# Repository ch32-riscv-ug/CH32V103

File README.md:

# CH32V103

<!-- This file is generated from ch32-riscv-ug/ch32-device-data (index/ + evidence/ + tools/build_readme.py). Edit there, not here. -->

[Choose a part](#product-comparison) &middot; [Pin viewer](https://ch32-riscv-ug.github.io/ch32-device-data/pins.html?chip=CH32V103) &middot; [Pin maps](#pin-maps--alternate-functions) &middot; [Examples](#evt-examples) &middot; [Documents](#documents) &middot; [Address map](#address-map)

## Quick start

Programming and debug: **2-wire SDI** (WCH-Link, `Serial Debug Interface`).

### Debug / serial defaults

Where these land **without writing a remap register**. SWD is live at reset; the UART pads are not -- the pin must still be put into alternate-function mode. See `route` in evidence/README.ja.md.

| Series | SWDIO | SWCLK | UART TX | UART RX |
|---|---|---|---|---|
| CH32V103 | PA13 | PA14 | PA9 (USART1); PA2 (USART2) | PA10 (USART1); PA3 (USART2) |

## Series

Flash and SRAM list every value the series has; more than one means it varies by part number, and the per-part values are in the comparison table below.

| Series | Core | ISA | Flash | SRAM | Main clock | VDD | Packages | Products | Official |
|---|---|---|---|---|---|---|---|---|---|
| **CH32V103** | QingKe V3A | RV32IMAC | 32K/64K | 10K/20K | 80 MHz | 2.7-5.5V | LQFP48,LQFP64M,QFN48X7 | 4 | [en](https://www.wch-ic.com/products/CH32V103.html) / [zh](https://www.wch.cn/products/CH32V103.html) |

## Product comparison

### CH32V103 product comparison

Only the 8 rows that differ between these 4 products; the other 7 are the same for all of them.

| | [CH32V103&#8203;C6T6](https://ch32-riscv-ug.github.io/ch32-device-data/pins.html?chip=CH32V103C6T6)&#8203;(LQFP48) | [CH32V103&#8203;C8T6](https://ch32-riscv-ug.github.io/ch32-device-data/pins.html?chip=CH32V103C8T6)&#8203;(LQFP48) | [CH32V103&#8203;C8U6](https://ch32-riscv-ug.github.io/ch32-device-data/pins.html?chip=CH32V103C8U6)&#8203;(QFN48X7) | [CH32V103&#8203;R8T6](https://ch32-riscv-ug.github.io/ch32-device-data/pins.html?chip=CH32V103R8T6)&#8203;(LQFP64M) |
|---|---|---|---|---|
| **Flash** | 32K | 64K | 64K | 64K |
| **SRAM** | 10K | 20K | 20K | 20K |
| **GPIO** | 37 | 37 | 37 | 51 |
| Timer General-purpose | 2 | 3 | 3 | 3 |
| ADC/TKey (Number of channels) | 10 | 10 | 10 | 16 |
| SPI | 1 | 2 | 2 | 2 |
| I2C | 1 | 2 | 2 | 2 |
| USART | 2 | 3 | 3 | 3 |

<details><summary>All 15 rows</summary>

| | [CH32V103&#8203;C6T6](https://ch32-riscv-ug.github.io/ch32-device-data/pins.html?chip=CH32V103C6T6)&#8203;(LQFP48) | [CH32V103&#8203;C8T6](https://ch32-riscv-ug.github.io/ch32-device-data/pins.html?chip=CH32V103C8T6)&#8203;(LQFP48) | [CH32V103&#8203;C8U6](https://ch32-riscv-ug.github.io/ch32-device-data/pins.html?chip=CH32V103C8U6)&#8203;(QFN48X7) | [CH32V103&#8203;R8T6](https://ch32-riscv-ug.github.io/ch32-device-data/pins.html?chip=CH32V103R8T6)&#8203;(LQFP64M) |
|---|---|---|---|---|
| **Flash** | 32K | 64K | 64K | 64K |
| **SRAM** | 10K | 20K | 20K | 20K |
| **GPIO** | 37 | 37 | 37 | 51 |
| **Temperature** | -40..85C | -40..85C | -40..85C | -40..85C |
| Timer General-purpose | 2 | 3 | 3 | 3 |
| Timer Advanced | 1 | 1 | 1 | 1 |
| Watchdog (WDT) | 2 | 2 | 2 | 2 |
| Timer SysTick | 1 | 1 | 1 | 1 |
| ADC/TKey (Number of channels) | 10 | 10 | 10 | 16 |
| SPI | 1 | 2 | 2 | 2 |
| I2C | 1 | 2 | 2 | 2 |
| USART | 2 | 3 | 3 | 3 |
| USBHD 2.0FS | 1 | 1 | 1 | 1 |
| CPU clock frequency | Typical: 72MHz | Typical: 72MHz | Typical: 72MHz | Typical: 72MHz |
| Operating voltage | 2.7V~5.5V | 2.7V~5.5V | 2.7V~5.5V | 2.7V~5.5V |

</details>

## Packages & pinout drawings

Pinout drawings are in the datasheet (chapter *Pinouts*); each link opens at the page that carries the drawing:

| Package | Products | Datasheet | Outline |
|---|---|---|---|
| LQFP48 | CH32V103C6T6 | [en](https://ch32-riscv-ug.github.io/CH32V103/datasheet_en/CH32V103DS0.PDF#page=13) / [zh](https://ch32-riscv-ug.github.io/CH32V103/datasheet_zh/CH32V103DS0.PDF#page=11) | [drawing](https://raw.githubusercontent.com/ch32-riscv-ug/WCH-common/main/image/package_LQFP48.png) |
| LQFP48 | CH32V103C8T6 | [en](https://ch32-riscv-ug.github.io/CH32V103/datasheet_en/CH32V103DS0.PDF#page=13) / [zh](https://ch32-riscv-ug.github.io/CH32V103/datasheet_zh/CH32V103DS0.PDF#page=11) | [drawing](https://raw.githubusercontent.com/ch32-riscv-ug/WCH-common/main/image/package_LQFP48.png) |
| QFN48X7 | CH32V103C8U6 | [en](https://ch32-riscv-ug.github.io/CH32V103/datasheet_en/CH32V103DS0.PDF#page=13) / [zh](https://ch32-riscv-ug.github.io/CH32V103/datasheet_zh/CH32V103DS0.PDF#page=11) | [drawing](https://raw.githubusercontent.com/ch32-riscv-ug/WCH-common/main/image/package_QFN48X7.png) |
| LQFP64M | CH32V103R8T6 | [en](https://ch32-riscv-ug.github.io/CH32V103/datasheet_en/CH32V103DS0.PDF#page=13) / [zh](https://ch32-riscv-ug.github.io/CH32V103/datasheet_zh/CH32V103DS0.PDF#page=11) | [drawing](https://raw.githubusercontent.com/ch32-riscv-ug/WCH-common/main/image/package_LQFP64M.png) |

## Pin maps & alternate functions

> [!NOTE]
> These are the **pin-table superset**: the datasheet prints one pad table for every product that shares a pinout, so a pad row does not mean this part has the peripheral. Use the product comparison table above for what a given part number contains.

### CH32V103 pin map

Pin functions (filterable): [ALL](https://ch32-riscv-ug.github.io/ch32-device-data/pins.html?chip=CH32V103) [ADC](https://ch32-riscv-ug.github.io/ch32-device-data/pins.html?chip=CH32V103&features=ADC) [I2C](https://ch32-riscv-ug.github.io/ch32-device-data/pins.html?chip=CH32V103&features=I2C) [SPI](https://ch32-riscv-ug.github.io/ch32-device-data/pins.html?chip=CH32V103&features=SPI) [SYS](https://ch32-riscv-ug.github.io/ch32-device-data/pins.html?chip=CH32V103&features=SYS) [TIM](https://ch32-riscv-ug.github.io/ch32-device-data/pins.html?chip=CH32V103&features=TIM) [UART](https://ch32-riscv-ug.github.io/ch32-device-data/pins.html?chip=CH32V103&features=UART) [USB](https://ch32-riscv-ug.github.io/ch32-device-data/pins.html?chip=CH32V103&features=USB)

| Pin name | Type | [CH32V103&#8203;C6T6](https://ch32-riscv-ug.github.io/ch32-device-data/pins.html?chip=CH32V103C6T6)&#8203;(LQFP48) | [CH32V103&#8203;C8T6](https://ch32-riscv-ug.github.io/ch32-device-data/pins.html?chip=CH32V103C8T6)&#8203;(LQFP48) | [CH32V103&#8203;C8U6](https://ch32-riscv-ug.github.io/ch32-device-data/pins.html?chip=CH32V103C8U6)&#8203;(QFN48X7) | [CH32V103&#8203;R8T6](https://ch32-riscv-ug.github.io/ch32-device-data/pins.html?chip=CH32V103R8T6)&#8203;(LQFP64M) | Notes |
|---|---|---|---|---|---|---|
| PA1 | I/O/A | 11 | 11 | 11 | 15 |  |
| PA2 | I/O/A | 12 | 12 | 12 | 16 | UART TX (USART2) |
| PA3 | I/O/A | 13 | 13 | 13 | 17 | UART RX (USART2) |
| PA4 | I/O/A | 14 | 14 | 14 | 20 |  |
| PA5 | I/O/A | 15 | 15 | 15 | 21 |  |
| PA6 | I/O/A | 16 | 16 | 16 | 22 |  |
| PA7 | I/O/A | 17 | 17 | 17 | 23 |  |
| PA8 | I/O | 29 | 29 | 29 | 41 |  |
| PA9 | I/O | 30 | 30 | 30 | 42 | UART TX (USART1) |
| PA10 | I/O | 31 | 31 | 31 | 43 | UART RX (USART1) |
| PA11 | I/O/A | 32 | 32 | 32 | 44 |  |
| PA12 | I/O/A | 33 | 33 | 33 | 45 |  |
| PA13 | I/O | 34 | 34 | 34 | 46 | SWDIO |
| PA14 | I/O | 37 | 37 | 37 | 49 | SWCLK |
| PA15 | I/O | 38 | 38 | 38 | 50 |  |
| PB0 | I/O/A | 18 | 18 | 18 | 26 |  |
| PB1 | I/O/A | 19 | 19 | 19 | 27 |  |
| PB2 | I/O | 20 | 20 | 20 | 28 |  |
| PB3 | I/O | 39 | 39 | 39 | 55 |  |
| PB4 | I/O | 40 | 40 | 40 | 56 |  |
| PB5 | I/O | 41 | 41 | 41 | 57 |  |
| PB6 | I/O/A | 42 | 42 | 42 | 58 |  |
| PB7 | I/O/A | 43 | 43 | 43 | 59 |  |
| PB8 | I/O/A | 45 | 45 | 45 | 61 |  |
| PB9 | I/O/A | 46 | 46 | 46 | 62 |  |
| PB10 | I/O | 21 | 21 | 21 | 29 |  |
| PB11 | I/O | 22 | 22 | 22 | 30 |  |
| PB12 | I/O | 25 | 25 | 25 | 33 |  |
| PB13 | I/O | 26 | 26 | 26 | 34 |  |
| PB14 | I/O | 27 | 27 | 27 | 35 |  |
| PB15 | I/O | 28 | 28 | 28 | 36 |  |
| PC0 | I/O/A | - | - | - | 8 |  |
| PC1 | I/O/A | - | - | - | 9 |  |
| PC2 | I/O/A | - | - | - | 10 |  |
| PC3 | I/O/A | - | - | - | 11 |  |
| PC4 | I/O/A | - | - | - | 24 |  |
| PC5 | I/O/A | - | - | - | 25 |  |
| PC6 | I/O | - | - | - | 37 |  |
| PC7 | I/O | - | - | - | 38 |  |
| PC8 | I/O | - | - | - | 39 |  |
| PC9 | I/O | - | - | - | 40 |  |
| PC10 | I/O | - | - | - | 51 |  |
| PC11 | I/O | - | - | - | 52 |  |
| PC12 | I/O | - | - | - | 53 |  |
| PD2 | I/O | - | - | - | 54 |  |
| BOOT0 | I | 44 | 44 | 44 | 60 |  |
| NRST | I/O | 7 | 7 | 7 | 7 |  |
| OSC8M_IN | I/A | 5 | - | - | - |  |
| OSC8M_OUT | O/A | 6 | - | - | - |  |
| OSC_IN | I/A | - | 5 | 5 | 5 |  |
| OSC_OUT | O/A | - | 6 | 6 | 6 |  |
| PA0-WKUP | I/O/A | 10 | 10 | 10 | 14 |  |
| PC13-TAMPER-RTC | I/O | 2 | 2 | 2 | 2 |  |
| PC14-OSC32_IN | I/O/A | 3 | 3 | 3 | 3 | OSC |
| PC15-OSC32_OUT | I/O/A | 4 | 4 | 4 | 4 | OSC |
| VBAT | P | 1 | 1 | 1 | 1 |  |
| VDDA | P | 9 | 9 | 9 | 13 |  |
| VDD_1 | P | 24 | 24 | 24 | 32 |  |
| VDD_2 | P | 36 | 36 | 36 | 48 |  |
| VDD_3 | P | 48 | 48 | 48 | 64 |  |
| VDD_4 | P | - | - | - | 19 |  |
| VSSA | P | 8 | 8 | 8 | 12 |  |
| VSS_1 | P | 23 | 23 | 23 | 31 |  |
| VSS_2 | P | 35 | 35 | 35 | 47 |  |
| VSS_3 | P | 47 | 47 | 47 | 63 |  |
| VSS_4 | P | - | - | - | 18 |  |

<details><summary><b>CH32V103 alternate functions</b></summary>

| Pad | default | (no route stated) | remap-1 |
|---|---|---|---|
| PA1 | ADC_IN1, TIM2_CH2, USART2_RTS | - | - |
| PA2 | ADC_IN2, TIM2_CH3, USART2_TX | - | - |
| PA3 | ADC_IN3, TIM2_CH4, USART2_RX | - | - |
| PA4 | ADC_IN4, SPI1_NSS, USART2_CK | - | - |
| PA5 | ADC_IN5, SPI1_SCK | - | - |
| PA6 | ADC_IN6, SPI1_MISO, TIM3_CH1 | - | TIM1_BKIN |
| PA7 | ADC_IN7, SPI1_MOSI, TIM3_CH2 | - | TIM1_CH1N |
| PA8 | MCO, TIM1_CH1, USART1_CK | - | - |
| PA9 | TIM1_CH2, USART1_TX | - | - |
| PA10 | TIM1_CH3, USART1_RX | - | - |
| PA11 | TIM1_CH4, USART1_CTS, USBHDM | - | - |
| PA12 | TIM1_ETR, USART1_RTS, USBHDP | - | - |
| PA13 | - | PA13 | - |
| PA14 | - | PA14 | - |
| PA15 | - | - | SPI1_NSS, TIM2_CH1, TIM2_ETR |
| PB0 | ADC_IN8, TIM3_CH3 | - | TIM1_CH2N |
| PB1 | ADC_IN9, TIM3_CH4 | - | TIM1_CH3N |
| PB3 | - | - | SPI1_SCK, TIM2_CH2 |
| PB4 | - | - | SPI1_MISO, TIM3_CH1 |
| PB5 | I2C1_SMBAI | - | SPI1_MOSI, TIM3_CH2 |
| PB6 | I2C1_SCL, TIM4_CH1 | - | USART1_TX |
| PB7 | I2C1_SDA, TIM4_CH2 | - | USART1_RX |
| PB8 | TIM4_CH3 | - | I2C1_SCL |
| PB9 | TIM4_CH4 | - | I2C1_SDA |
| PB10 | I2C2_SCL, USART3_TX | - | TIM2_CH3 |
| PB11 | I2C2_SDA, USART3_RX | - | TIM2_CH4 |
| PB12 | I2C2_SMBAI, SPI2_NSS, TIM1_BKIN, USART3_CK | - | - |
| PB13 | SPI2_SCK, TIM1_CH1N, USART3_CTS | - | - |
| PB14 | SPI2_MISO, TIM1_CH2N, USART3_RTS | - | - |
| PB15 | SPI2_MOSI, TIM1_CH3N | - | - |
| PC0 | ADC_IN10 | - | - |
| PC1 | ADC_IN11 | - | - |
| PC2 | ADC_IN12 | - | - |
| PC3 | ADC_IN13 | - | - |
| PC4 | ADC_IN14 | - | - |
| PC5 | ADC_IN15 | - | - |
| PC6 | - | - | TIM3_CH1 |
| PC7 | - | - | TIM3_CH2 |
| PC8 | - | - | TIM3_CH3 |
| PC9 | - | - | TIM3_CH4 |
| PC10 | - | - | USART3_TX |
| PC11 | - | - | USART3_RX |
| PC12 | - | - | USART3_CK |
| PD2 | TIM3_ETR | - | - |
| OSC8M_IN | - | PD0 | - |
| OSC8M_OUT | - | PD1 | - |
| OSC_IN | - | PD0 | - |
| OSC_OUT | - | PD1 | - |
| PA0-WKUP | ADC_IN0, TIM2_CH1, TIM2_ETR, USART2_CTS, WKUP | - | - |
| PC13-TAMPER-RTC | TAMPER-RTC | - | - |
| PC14-OSC32_IN | OSC32_IN | - | - |
| PC15-OSC32_OUT | OSC32_OUT | - | - |

</details>

<details><summary><b>Remap selectors (AFIO)</b></summary>

| Series | Field | Register | Bits | Values | Reset |
|---|---|---|---|---|---|
| CH32V103 | I2C1_REMAP | PCFR1 | PCFR1:1 | 0;1 | 0 |
| CH32V103 | SPI1_REMAP | PCFR1 | PCFR1:0 | 0;1 | 0 |
| CH32V103 | TIM1_REMAP | PCFR1 | PCFR1:6;PCFR1:7 | 0;1;2;3 | 0 |
| CH32V103 | TIM2_REMAP | PCFR1 | PCFR1:8;PCFR1:9 | 0;1;2;3 | 0 |
| CH32V103 | TIM3_REMAP | PCFR1 | PCFR1:10;PCFR1:11 | 0;2;3 | 0 |
| CH32V103 | TIM4_REMAP | PCFR1 | PCFR1:12 | 0;1 |  |
| CH32V103 | USART1_REMAP | PCFR1 | PCFR1:2 | 0;1 | 0 |
| CH32V103 | USART2_REMAP | PCFR1 | PCFR1:3 | 0;1 |  |
| CH32V103 | USART3_REMAP | PCFR1 | PCFR1:4;PCFR1:5 | 0;1;2;3 | 0 |

</details>

## Block diagrams

### CH32V103

## EVT examples

94 routines in [EVT/EXAM](https://github.com/ch32-riscv-ug/CH32V103/tree/main/EVT/EXAM):

[ADC](https://github.com/ch32-riscv-ug/CH32V103/tree/main/EVT/EXAM/ADC) 8 · [APPLICATION](https://github.com/ch32-riscv-ug/CH32V103/tree/main/EVT/EXAM/APPLICATION) 2 · [BKP](https://github.com/ch32-riscv-ug/CH32V103/tree/main/EVT/EXAM/BKP) 1 · [CRC](https://github.com/ch32-riscv-ug/CH32V103/tree/main/EVT/EXAM/CRC) 1 · [DMA](https://github.com/ch32-riscv-ug/CH32V103/tree/main/EVT/EXAM/DMA) 2 · [EXTI](https://github.com/ch32-riscv-ug/CH32V103/tree/main/EVT/EXAM/EXTI) 1 · [FLASH](https://github.com/ch32-riscv-ug/CH32V103/tree/main/EVT/EXAM/FLASH) 1 · [FreeRTOS](https://github.com/ch32-riscv-ug/CH32V103/tree/main/EVT/EXAM/FreeRTOS) 1 · [GPIO](https://github.com/ch32-riscv-ug/CH32V103/tree/main/EVT/EXAM/GPIO) 1 · [HarmonyOS](https://github.com/ch32-riscv-ug/CH32V103/tree/main/EVT/EXAM/HarmonyOS) 1 · [I2C](https://github.com/ch32-riscv-ug/CH32V103/tree/main/EVT/EXAM/I2C) 6 · [IAP](https://github.com/ch32-riscv-ug/CH32V103/tree/main/EVT/EXAM/IAP) 1 · [INT](https://github.com/ch32-riscv-ug/CH32V103/tree/main/EVT/EXAM/INT) 2 · [IWDG](https://github.com/ch32-riscv-ug/CH32V103/tree/main/EVT/EXAM/IWDG) 1 · [PWR](https://github.com/ch32-riscv-ug/CH32V103/tree/main/EVT/EXAM/PWR) 5 · [RCC](https://github.com/ch32-riscv-ug/CH32V103/tree/main/EVT/EXAM/RCC) 5 · [RT-Thread](https://github.com/ch32-riscv-ug/CH32V103/tree/main/EVT/EXAM/RT-Thread) 1 · [RTC](https://github.com/ch32-riscv-ug/CH32V103/tree/main/EVT/EXAM/RTC) 2 · [SPI](https://github.com/ch32-riscv-ug/CH32V103/tree/main/EVT/EXAM/SPI) 7 · [SYSTICK](https://github.com/ch32-riscv-ug/CH32V103/tree/main/EVT/EXAM/SYSTICK) 1 · [TIM](https://github.com/ch32-riscv-ug/CH32V103/tree/main/EVT/EXAM/TIM) 16 · [TOUCHKEY](https://github.com/ch32-riscv-ug/CH32V103/tree/main/EVT/EXAM/TOUCHKEY) 1 · [TencentOS](https://github.com/ch32-riscv-ug/CH32V103/tree/main/EVT/EXAM/TencentOS) 1 · [USART](https://github.com/ch32-riscv-ug/CH32V103/tree/main/EVT/EXAM/USART) 9 · [USB](https://github.com/ch32-riscv-ug/CH32V103/tree/main/EVT/EXAM/USB) 16 · [WWDG](https://github.com/ch32-riscv-ug/CH32V103/tree/main/EVT/EXAM/WWDG) 1

## Documents

| Document | Kind | English | 中文 |
|---|---|---|---|
| CH32V103DS0.PDF | datasheet | [page](https://www.wch-ic.com/downloads/CH32V103DS0_PDF.html) [mirror](https://ch32-riscv-ug.github.io/CH32V103/datasheet_en/CH32V103DS0.PDF) v1.2 | [page](https://www.wch.cn/downloads/CH32V103DS0_PDF.html) [mirror](https://ch32-riscv-ug.github.io/CH32V103/datasheet_zh/CH32V103DS0.PDF) v1.2 |
| CH32xRM.PDF | reference-manual | [page](https://www.wch-ic.com/downloads/CH32xRM_PDF.html) [mirror](https://ch32-riscv-ug.github.io/CH32V103/datasheet_en/CH32xRM.PDF) v2.0 | [page](https://www.wch.cn/downloads/CH32xRM_PDF.html) [mirror](https://ch32-riscv-ug.github.io/CH32V103/datasheet_zh/CH32xRM.PDF) v2.0 |
| CH32V103EVT.ZIP | evt | - | [page](https://www.wch.cn/downloads/CH32V103EVT_ZIP.html) [mirror](https://github.com/ch32-riscv-ug/CH32V103/tree/main/EVT) v2.8 |

### Evaluation boards

- board-manual:en: [CH32V103 Evaluation Board Reference-EN.pdf](https://github.com/ch32-riscv-ug/CH32V103/blob/main/EVT/PUB/CH32V103%20Evaluation%20Board%20Reference-EN.pdf)
- board-manual:zh: [CH32V103评估板说明书.pdf](https://github.com/ch32-riscv-ug/CH32V103/blob/main/EVT/PUB/CH32V103%E8%AF%84%E4%BC%B0%E6%9D%BF%E8%AF%B4%E6%98%8E%E4%B9%A6.pdf)
- schematic-pdf: [CH32V103SCH.pdf](https://github.com/ch32-riscv-ug/CH32V103/blob/main/EVT/PUB/CH32V103SCH.pdf)

4 board schematics under `EVT/PUB/SCHPCB/`: `CH32V103C_R0`, `CH32V103C_R1`, `CH32V103R_R0`, `CH32V103R_R1`

## Reference

### Address map

| Region | Base | Kind |
|---|---|---|
| APB1PERIPH | `0x40000000` | bus |
| PERIPH | `0x40000000` | bus |
| APB2PERIPH | `0x40010000` | bus |
| AHBPERIPH | `0x40020000` | bus |
| FLASH | `0x00000000` | link-origin |
| RAM | `0x20000000` | link-origin |
| FLASH | `0x08000000` | memory |
| OB | `0x1ffff800` | memory |
| SRAM | `0x20000000` | memory |

`link-origin` is what the EVT linker scripts use; the `memory` row for FLASH is the address the device header states. Both windows are real -- CH32V307 answers at `0x08000000` and at `0x00000000`.

Peripheral base addresses are in [memory_map.csv](https://github.com/ch32-riscv-ug/ch32-device-data/blob/main/evidence/memory_map.csv); interrupt numbers in [interrupts.csv](https://github.com/ch32-riscv-ug/ch32-device-data/blob/main/evidence/interrupts.csv).

---
Data: [ch32-device-data](https://github.com/ch32-riscv-ug/ch32-device-data) (evidence/ and index/ -- each value carries its evidence and confidence there).

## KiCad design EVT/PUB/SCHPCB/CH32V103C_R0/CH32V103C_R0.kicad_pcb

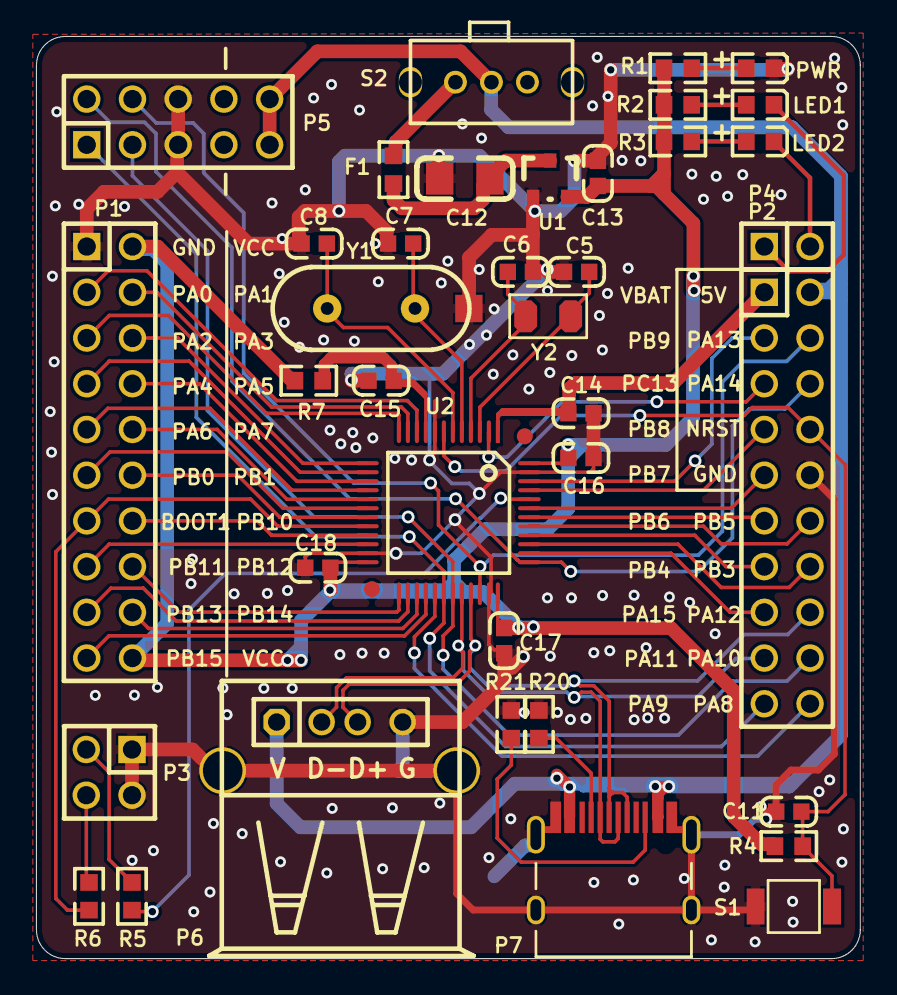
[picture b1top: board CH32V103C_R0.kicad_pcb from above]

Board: 2 copper layers, 45.8 x 51.2 mm, 38 parts (0 on the bottom side), 55 nets.

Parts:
C5, C6: 12pF; 0603_C
C7, C8: 22pF; 0603_C
C11, C14, C15, C16, C17, C18: 0.1uF; 0603_C
C12: 10uF; 3216_C
C13: 2.2uF; 0603_C
F1: 500mA; 0603
LED1: LED1 blue; 0603+
LED2: LED2 blue; 0603+
P1, P2: Header 10X2; IDC20-2.54mm
P3: HEADER 2x2; IDC4-2.54MM
P4: 2HEAD; SIP2-2.54mm
P5: HEADER 5x2; IDC10-2.54mm
P6: USB_A; USBAF
P7: TYPE-C; TYPE-C-Receptacle-2.0
PWR: POWER red; 0603+
R1, R2, R3: 1K; 0603
R4, R5, R6: 10K; 0603
R7: 0Ω; 0603
R20, R21: NC(5.1K); 0603
S1: KEY; 贴片按键
S2: SW; KEY2
U1: 6219P33M; SOT-23
U2: CH32V103C; LQFP48
Y1: 8M; XT_AT49
Y2: 32.768k; FC-135

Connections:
+5V: P2.2, P5.9, P5.10, P6.1, P7.A4, P7.B4, S2.1
BOOT0: R5.1, U2.44
BOOT1: P1.13, R6.1, U2.20
GND: C5.1, C6.2, C7.1, C8.1, C11.1, C12.2, C13.1, C14.2, C15.2, C16.1, C17.1, C18.1, P1.1, P2.10, P3.1, P3.2, P5.5, P5.6, P6.0, P6.4, P7.0, P7.A1, P7.B1, PWR.2, R20.2, R21.2, S1.3, U1.1, U2.8, U2.23, U2.35, U2.47, Y1.0
LED1: LED1.2, P4.1
LED2: LED2.2, P4.2
NRST: C11.2, P2.8, R4.1, S1.1, U2.7
NetC12_1: C12.1, F1.2, U1.3
NetF1_1: F1.1, S2.3
NetLED1_1: LED1.1, R2.2
NetLED2_1: LED2.1, R3.2
NetP3_3: P3.3, R5.2
NetP3_4: P3.4, R6.2
NetP7_A5: P7.A5, R20.1
NetP7_B5: P7.B5, R21.1
NetPWR_1: PWR.1, R1.1
PA0: P1.3, U2.10
PA1: P1.4, U2.11
PA2: P1.5, U2.12
PA3: P1.6, U2.13
PA4: P1.7, U2.14
PA5: P1.8, U2.15
PA6: P1.9, U2.16
PA7: P1.10, U2.17
PA8: P2.20, U2.29
PA9: P2.19, P5.1, U2.30
PA10: P2.18, P5.3, U2.31
PA11: P2.17, P6.2, P7.A7, P7.B7, U2.32
PA12: P2.16, P6.3, P7.A6, P7.B6, U2.33
PA13: P2.4, P5.4, U2.34
PA14: P2.6, P5.2, U2.37
PA15: P2.15, U2.38
PB0: P1.11, U2.18
PB1: P1.12, U2.19
PB3: P2.14, U2.39
PB4: P2.13, U2.40
PB5: P2.12, U2.41
PB6: P2.11, U2.42
PB7: P2.9, U2.43
PB8: P2.7, U2.45
PB9: P2.3, U2.46
PB10: P1.14, U2.21
PB11: P1.15, U2.22
PB12: P1.16, U2.25
PB13: P1.17, U2.26
PB14: P1.18, U2.27
PB15: P1.19, U2.28
PC13: P2.5, U2.2
PC14: C5.2, U2.3, Y2.1
PC15: C6.1, U2.4, Y2.2
PD0: C7.2, U2.5, Y1.2
PD1: C8.2, U2.6, Y1.1
VBAT: C14.1, P2.1, U2.1
VCC: C13.2, C16.2, C17.2, C18.2, P1.2, P1.20, R1.2, R2.1, R3.1, R4.2, R7.1, U1.2, U2.24, U2.36, U2.48
VDDA: C15.1, R7.2, U2.9

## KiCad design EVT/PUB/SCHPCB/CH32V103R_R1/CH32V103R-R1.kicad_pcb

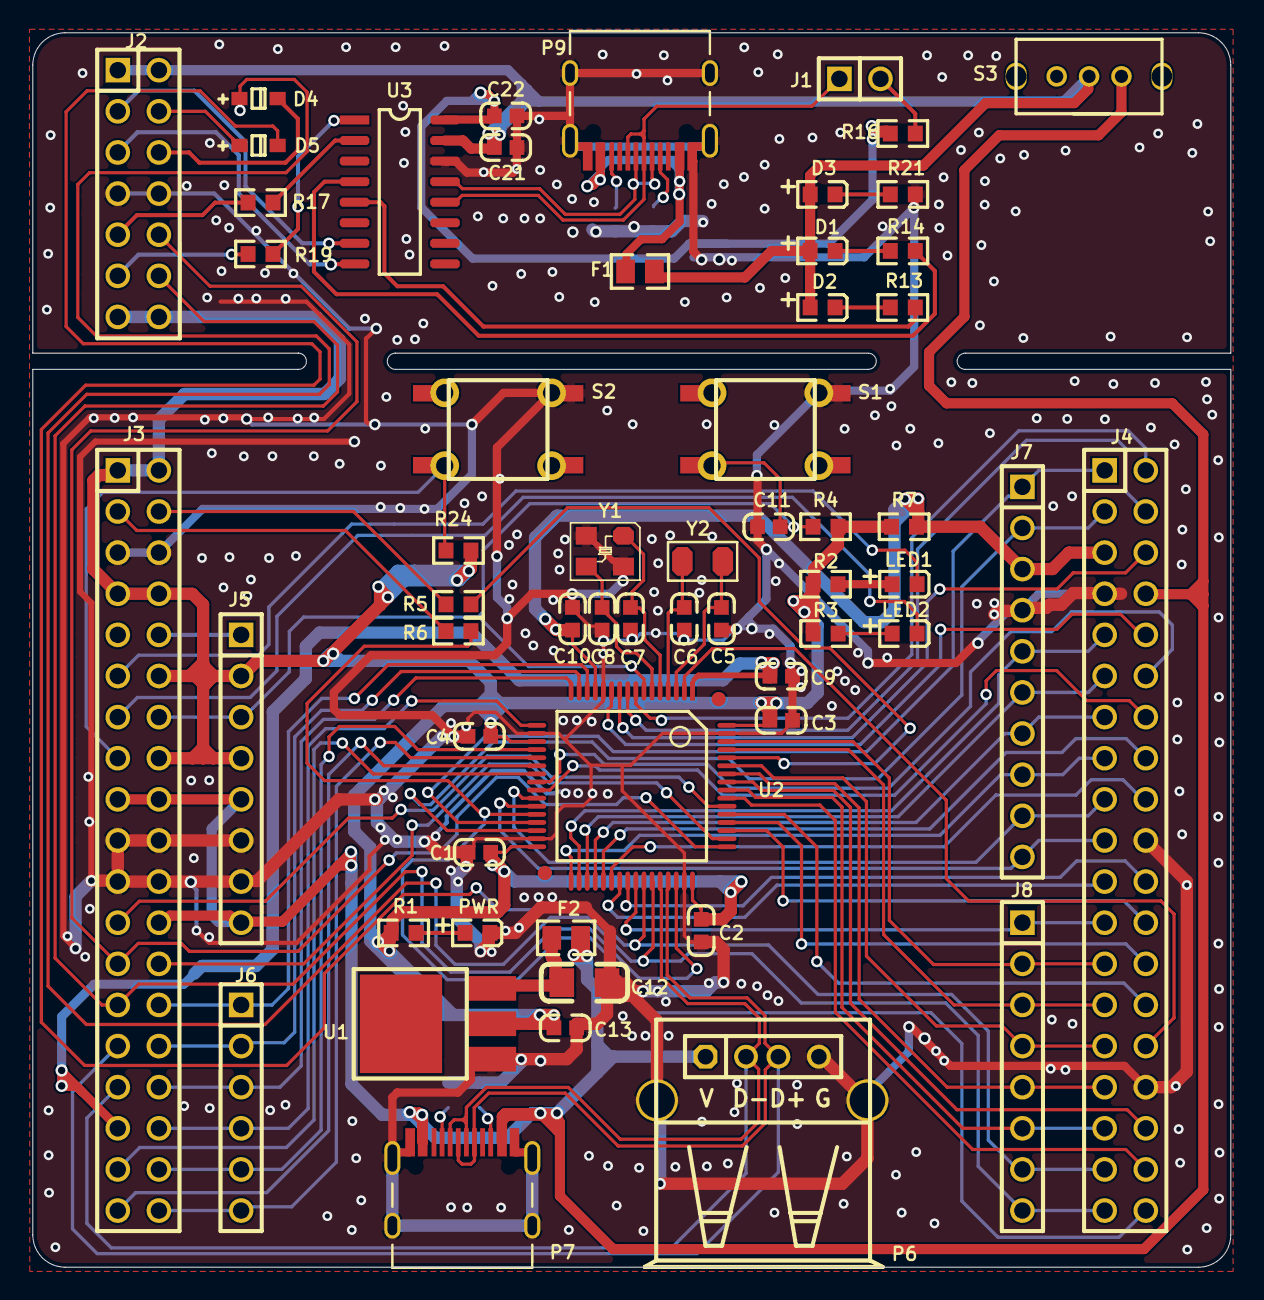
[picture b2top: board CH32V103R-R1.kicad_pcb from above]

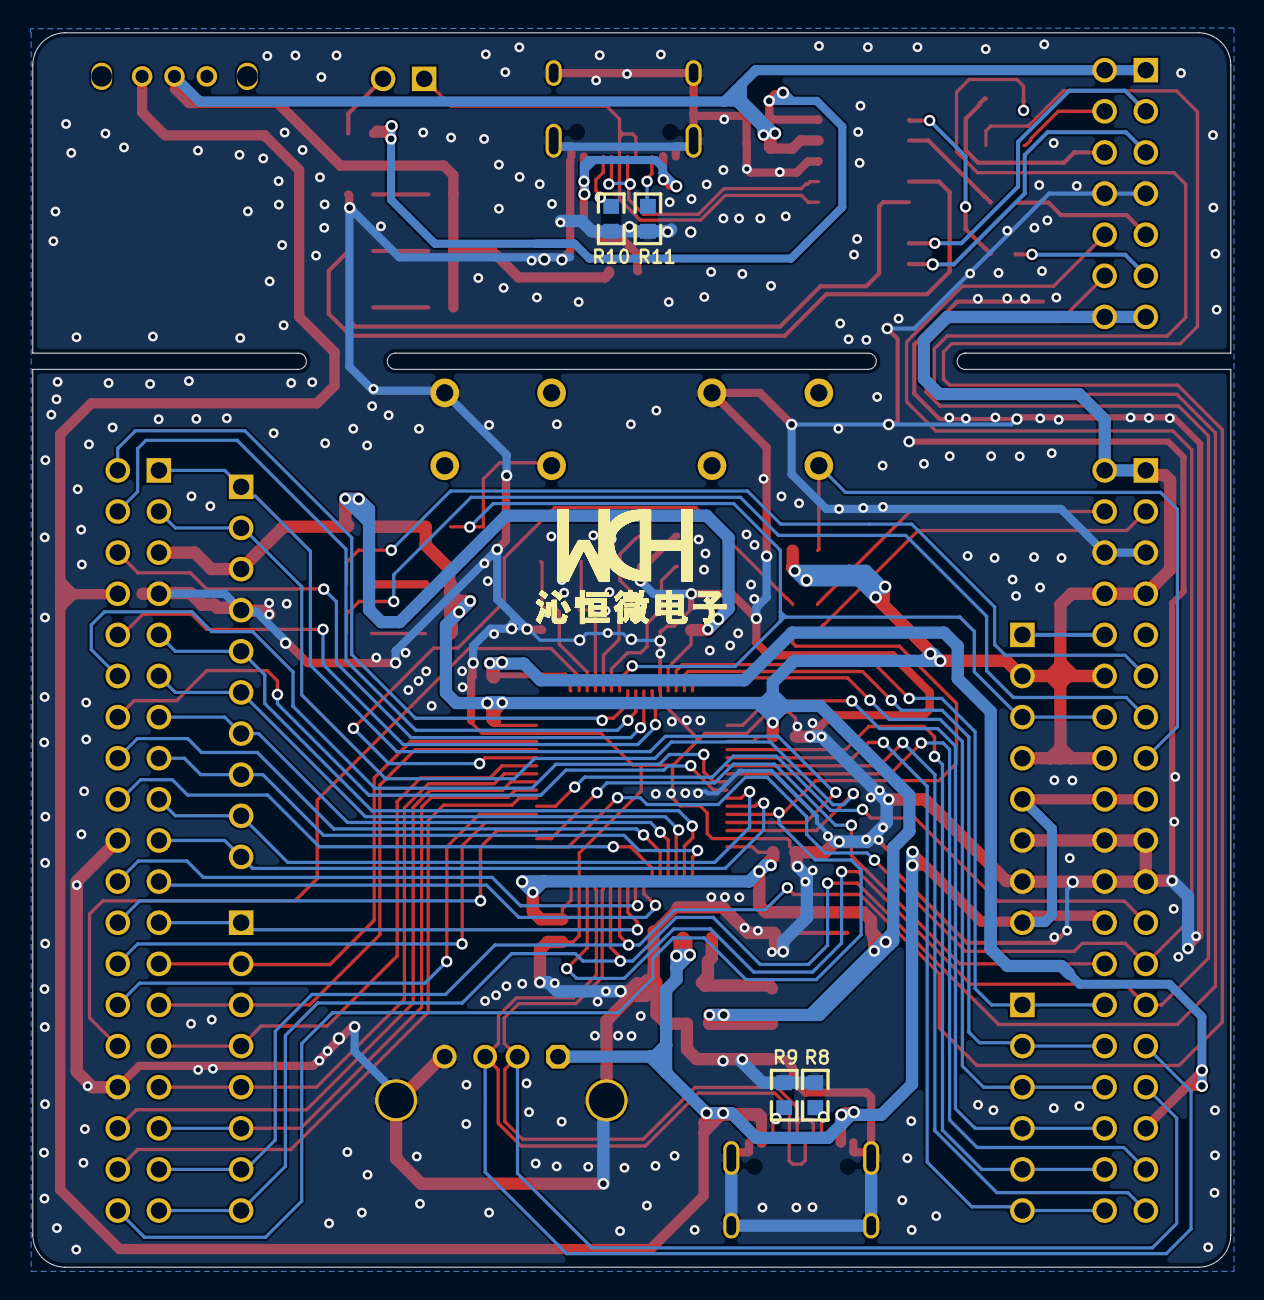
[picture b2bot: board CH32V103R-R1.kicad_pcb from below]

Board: 2 copper layers, 74.0 x 76.3 mm, 62 parts (4 on the bottom side), 91 nets.

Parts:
C1, C2, C3, C4, C9, C10, C11, C21, C22: 0.1uF; 0603_C
C5, C6: 12pF; 0603_C
C7, C8: 22pF; 0603_C
C12: 10uF; 3216_C
C13: 10uF; 0603_C
D1: GREEN; 0603+
D2: BLUE; 0603+
D3: RED; 0603+
D4, D5: B0520; SOD-323
F1, F2: 500mA; 0805
J1: Header 2; SIP2-2.54MM
J2: Header 7X2; IDC14-2.54mm
J3, J4: Header 19X2; IDC38-2.54mm
J5, J8: Header 8; SIP8-2.54mm
J6: Header 6; SIP6-2.54MM
J7: Header 10; SIP10-2.54mm
LED1: LED1 blue; 0603+
LED2: LED2 blue; 0603+
P6: USB_A; USBAF
P7, P9: TYPE-C; TYPE-C-Receptacle-2.0
PWR: POWER red; 0603+
R1, R2, R3, R13, R21: 1K; 0603
R4, R5, R6, R14, R24: 10K; 0603
R7: 0Ω; 0603
R8, R9, R10, R11: NC(5.1K); 0603
R16: 4.7K; 0603
R17, R19: 270; 0603
S1: RESET(Yellow); KEYX
S2: USER(Blue); KEYX
S3: SW; KEY2
U1: 1117-3.3V; SOT-223
U2: CH32V103R; LQFP64M_10X10
U3: CH549G; SOP16
Y1: 8M; XT3225
Y2: 32.768k; FC-135

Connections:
5V: C21.1, D1.1, D2.1, D3.1, F1.2, J2.1, J2.2, S3.1, U3.15
5V_USB: F1.1, P9.A4, P9.B4
+5V: F2.1, J3.17, J3.18, J3.24, J4.8, J5.5, J5.8, P6.1, P7.A4, P7.B4, S3.3
BOOT0: R5.2, U2.60
BOOT1: J4.38, R6.1, U2.28
CLK: J2.10, J3.25, U2.49
CLK0: J2.9, R17.1
DIO: J2.12, J3.27, U2.46
DIO0: J2.11, R19.1
D_SWCLK: R17.2, U3.2
D_SWDIO: R19.2, U3.1
GND: C1.1, C2.1, C3.1, C4.1, C5.2, C6.2, C7.1, C8.1, C9.2, C10.2, C11.1, C12.2, C13.2, C21.2, C22.2, J2.7, J2.8, J3.5, J3.6, J3.19, J3.20, J3.21, J3.22, J4.7, J4.20, J4.32, J5.6, J5.7, J7.4, P6.0, P6.4, P7.0, P7.A1, P7.B1, P9.0, P9.A1, P9.B1, PWR.2, R8.1, R9.1, R10.2, R11.2, R21.1, S1.3, S2.3, U1.1, U2.12, U2.18, U2.31, U2.47, U2.63, U3.14, Y1.2, Y1.4
KEY: J3.15, R24.1, S2.1
LED1: J3.11, LED1.2
LED2: J3.13, LED2.2
LED_CON: R13.1, U3.5
LED_RUN: R14.1, U3.4
NRST: C11.2, J3.14, J5.3, R4.1, S1.1, U2.7
NetC12_1: C12.1, F2.2, U1.3
NetD1_2: D1.2, R14.2
NetD2_2: D2.2, R13.2
NetD3_2: D3.2, R21.2
NetJ1_2: J1.2, R16.1
NetJ3_3: J3.3, R6.2
NetJ3_4: J3.4, R5.1
NetJ3_10: J3.10, J5.1
NetLED1_1: LED1.1, R2.2
NetLED2_1: LED2.1, R3.2
NetP7_A5: P7.A5, R8.2
NetP7_B5: P7.B5, R9.2
NetP9_A5: P9.A5, R10.1
NetP9_B5: P9.B5, R11.1
NetPWR_1: PWR.1, R1.1
PA0: J3.28, J6.1, U2.14
PA1: J3.30, J6.2, U2.15
PA2: J3.32, J6.3, U2.16
PA3: J3.34, J6.4, U2.17
PA4: J3.36, J6.5, U2.20
PA5: J3.38, J6.6, U2.21
PA6: J3.37, U2.22
PA7: J3.35, U2.23
PA8: J4.23, J8.1, U2.41
PA9: D5.2, J4.35, J8.7, U2.42
PA10: D4.1, J4.37, J8.8, U2.43
PA11: J3.31, P6.2, P7.A7, P7.B7, U2.44
PA12: J3.29, P6.3, P7.A6, P7.B6, U2.45
PA15: J3.26, U2.50
PB0: J4.17, J7.9, U2.26
PB1: J4.19, J7.10, U2.27
PB3: J4.36, U2.55
PB4: J4.33, J8.6, U2.56
PB5: J4.34, U2.57
PB6: J4.31, J8.5, U2.58
PB7: J4.29, J8.4, U2.59
PB8: J4.27, J8.3, U2.61
PB9: J4.25, J8.2, U2.62
PB10: J4.1, J7.1, U2.29
PB11: J4.3, J7.2, U2.30
PB12: J4.15, J7.8, U2.33
PB13: J4.9, J7.5, U2.34
PB14: J4.11, J7.6, U2.35
PB15: J4.13, J7.7, U2.36
PC0: J4.2, U2.8
PC1: J4.4, U2.9
PC2: J4.6, U2.10
PC3: J4.10, U2.11
PC4: J4.12, U2.24
PC5: J4.14, U2.25
PC6: J4.16, U2.37
PC7: J4.18, U2.38
PC8: J4.21, U2.39
PC9: J4.22, U2.40
PC10: J4.24, U2.51
PC11: J4.26, U2.52
PC12: J4.28, U2.53
PC13: J4.30, U2.2
PC14: C5.1, U2.3, Y2.1
PC15: C6.1, U2.4, Y2.2
PD0: C7.2, U2.5, Y1.1
PD1: C8.2, U2.6, Y1.3
PD2: J3.23, U2.54
RX: D4.2, J2.6
RX0: J2.3, U3.7
TX: D5.1, J2.4
TX0: J2.5, U3.8
USB_N: P9.A7, P9.B7, U3.13
USB_P: J1.1, P9.A6, P9.B6, U3.12
V33: C22.1, R16.2, U3.16
VBAT: C9.1, J3.33, U2.1
VCC: C1.2, C2.2, C3.2, C4.2, C13.1, J2.13, J2.14, J3.1, J3.2, J3.7, J3.8, J3.12, J3.16, J5.2, J5.4, R1.2, R2.1, R3.1, R4.2, R7.1, R24.2, U1.2, U2.19, U2.32, U2.48, U2.64
VDDA: C10.1, J4.5, J7.3, R7.2, U2.13

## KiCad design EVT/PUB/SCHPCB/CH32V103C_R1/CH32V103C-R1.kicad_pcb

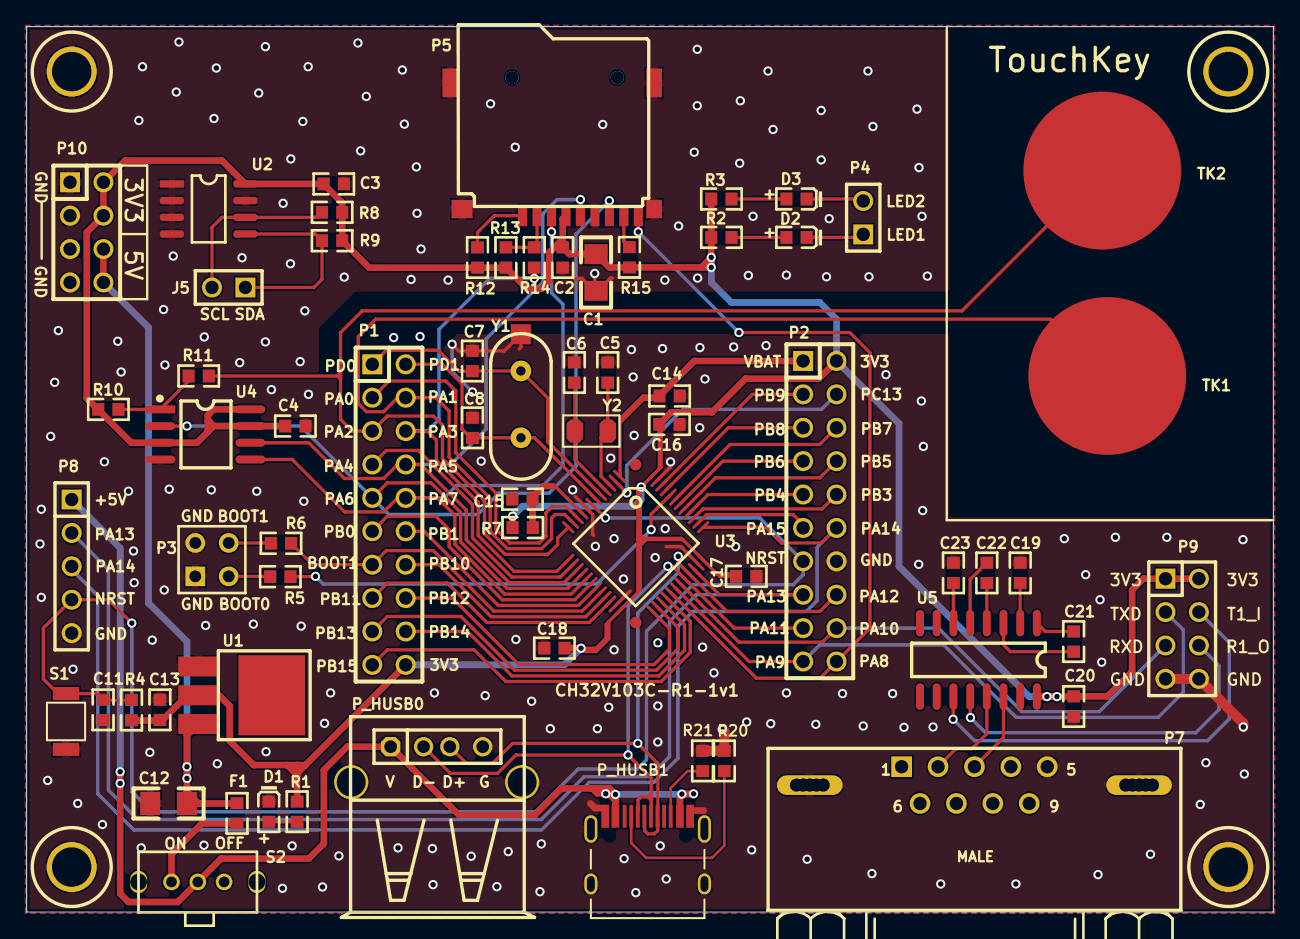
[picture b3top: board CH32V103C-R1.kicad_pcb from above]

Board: 2 copper layers, 94.8 x 67.3 mm, 65 parts (0 on the bottom side), 71 nets.

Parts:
C1, C12: 10uF; 3216
C2, C3, C4, C11, C14, C15, C16, C17, C18, C19, C20, C21, C22, C23: 0.1uF; 0603
C5, C6: 12pF; 0603
C7, C8: 22pF; 0603
C13: 10uF; 0603
D1: POWER; 0603+
D2: LED1 blue; 0603+
D3: LED2 blue; 0603+
F1: 500mA; 0603
J5: Header 2; SIP2-2.54mm
P1, P2: Header 10X2; IDC20-2.54mm
P3: Header 2X2; HDR2X2
P4: Header 2; SIP2-2.54mm
P5: TF_自弹; TF
P7: DB9; M
P8: Header 5; SIP5-2.54mm
P9: HEADER 4x2; IDC8-2.54mm
P10: Header 4X2; IDC8-2.54mm
P_HUSB0: USB_A; USBA-l
P_HUSB1: TYPE-C; TYPE-C-Receptacle-2.0
R1, R2, R3: 1K; 0603
R4, R5, R6, R8, R9, R10, R12, R13, R15: 10K; 0603
R7: 0Ω; 0603
R11, R14: NC(0Ω); 0603
R20, R21: NC(5.1K); 0603
S1: KEY; 贴片按键
S2: SW; KEY2
TK1: KEY6; TOUCHKEY-12mm
TK2: KEY7; TOUCHKEY-12mm
U1: 1117-3.3V; SOT-223
U2: 24C02; SOP8
U3: CH32V103C; LQFP48
U4: W25Q16; SOIC-8_208mil
U5: MAX3232; SOIC-16_150mil
Y1: 8M; 28
Y2: 32.768k; FC-135

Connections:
3V3: C1.1, C2.1, C3.2, C4.2, C13.1, C16.2, C17.2, C18.2, C20.2, P1.20, P2.2, P5.4, P9.1, P9.2, P10.2, P10.4, R1.2, R2.1, R3.1, R4.2, R7.1, R8.1, R9.1, R10.2, R12.2, R13.2, R15.1, U1.2, U2.8, U3.24, U3.36, U3.48, U4.3, U4.7, U4.8, U5.16
5V: C12.1, F1.2, P10.6, P10.8, U1.3
+5V: P8.1, P_HUSB0.1, P_HUSB1.A4, P_HUSB1.B4, S2.1
BOOT0: R5.1, U3.44
BOOT1: P1.13, R6.1, U3.20
GND: C1.2, C2.2, C3.1, C4.1, C5.2, C6.2, C7.1, C8.1, C11.1, C12.2, C13.2, C14.2, C15.2, C16.1, C17.1, C18.1, C19.2, C20.1, C23.2, D1.2, P2.14, P3.1, P3.2, P5.6, P5.10, P7.0, P7.5, P8.5, P9.7, P9.8, P10.1, P10.3, P10.5, P10.7, P_HUSB0.0, P_HUSB0.4, P_HUSB1.0, P_HUSB1.A1, P_HUSB1.B1, R20.2, R21.2, S1.3, U1.1, U2.1, U2.2, U2.3, U2.4, U2.7, U3.8, U3.23, U3.35, U3.47, U4.4, U5.15, Y1.0
IIC_SCL: J5.2, R8.2, U2.6
IIC_SDA: J5.1, R9.2, U2.5
LED1: D2.2, P4.1
LED2: D3.2, P4.2
NRST: C11.2, P2.13, P8.4, R4.1, S1.1, U3.7
NetC19_1: C19.1, U5.2
NetC21_1: C21.1, U5.1
NetC21_2: C21.2, U5.3
NetC22_1: C22.1, U5.4
NetC22_2: C22.2, U5.5
NetC23_1: C23.1, U5.6
NetD1_1: D1.1, R1.1
NetD2_1: D2.1, R2.2
NetD3_1: D3.1, R3.2
NetF1_1: F1.1, S2.2
NetP3_3: P3.3, R5.2
NetP3_4: P3.4, R6.2
NetP5_1: P5.1, R12.1
NetP5_2: P5.2, R13.1, R14.1
NetP5_8: P5.8, R15.2
NetP_HUSB1_A5: P_HUSB1.A5, R20.1
NetP_HUSB1_B5: P_HUSB1.B5, R21.1
NetR10_1: R10.1, R11.1, U4.1
PA0: P1.3, U3.10
PA1: P1.4, TK1.1, U3.11
PA2: P1.5, R11.2, TK2.1, U3.12
PA3: P1.6, R14.2, U3.13
PA4: P1.7, U3.14
PA5: P1.8, P5.5, U3.15, U4.6
PA6: P1.9, P5.7, U3.16, U4.2
PA7: P1.10, P5.3, U3.17, U4.5
PA8: P2.20, P5.9, U3.29
PA9: P2.19, P9.3, U3.30
PA10: P2.18, P9.5, U3.31
PA11: P2.17, P_HUSB0.2, P_HUSB1.A7, P_HUSB1.B7, U3.32
PA12: P2.16, P_HUSB0.3, P_HUSB1.A6, P_HUSB1.B6, U3.33
PA13: P2.15, P8.2, U3.34
PA14: P2.12, P8.3, U3.37
PA15: P2.11, U3.38
PB0: P1.11, U3.18
PB1: P1.12, U3.19
PB3: P2.10, U3.39
PB4: P2.9, U3.40
PB5: P2.8, U3.41
PB6: P2.7, U3.42
PB7: P2.6, U3.43
PB8: P2.5, U3.45
PB9: P2.3, U3.46
PB10: P1.14, U3.21
PB11: P1.15, U3.22
PB12: P1.16, U3.25
PB13: P1.17, U3.26
PB14: P1.18, U3.27
PB15: P1.19, U3.28
PC13: P2.4, U3.2
PC14: C5.1, U3.3, Y2.1
PC15: C6.1, U3.4, Y2.2
PD0: C7.2, P1.1, U3.5, Y1.2
PD1: C8.2, P1.2, U3.6, Y1.1
R1_OUT: P9.6, U5.12
RXD232: P7.3, U5.14
T1_IN: P9.4, U5.11
TXD232: P7.2, U5.13
VBAT: C14.1, P2.1, U3.1
VDDA: C15.1, R7.2, U3.9

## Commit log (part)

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2024-05-15 add image
2024-05-15 Rename architecture.png to architecture_CH32V103.png
2024-05-15 Rename system.png to system_CH32V103.png
2026-06-15 update update.sh and add GitHub Actions workflow for automated datasheet downloads
2026-06-15 update cron schedule for automated datasheet downloads to reduce server load
2026-06-15 refactor update job to simplify commit logic in GitHub Actions workflow
2026-06-16 update GitHub Actions schedule
2026-06-19 update GitHub Actions workflow to implement keepalive logic and remove unnecessary permissions
2026-06-19 refactor fetch function in update.sh to simplify error handling and remove retry logic
